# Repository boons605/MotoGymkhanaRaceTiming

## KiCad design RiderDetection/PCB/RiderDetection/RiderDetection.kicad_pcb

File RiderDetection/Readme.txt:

The embedded part of the rider detection was written for the ESP32 platform.
Development hardware used is the ESP32-WROOM-32.
Development environment/framework used is ESP-IDF v4.1-dirty

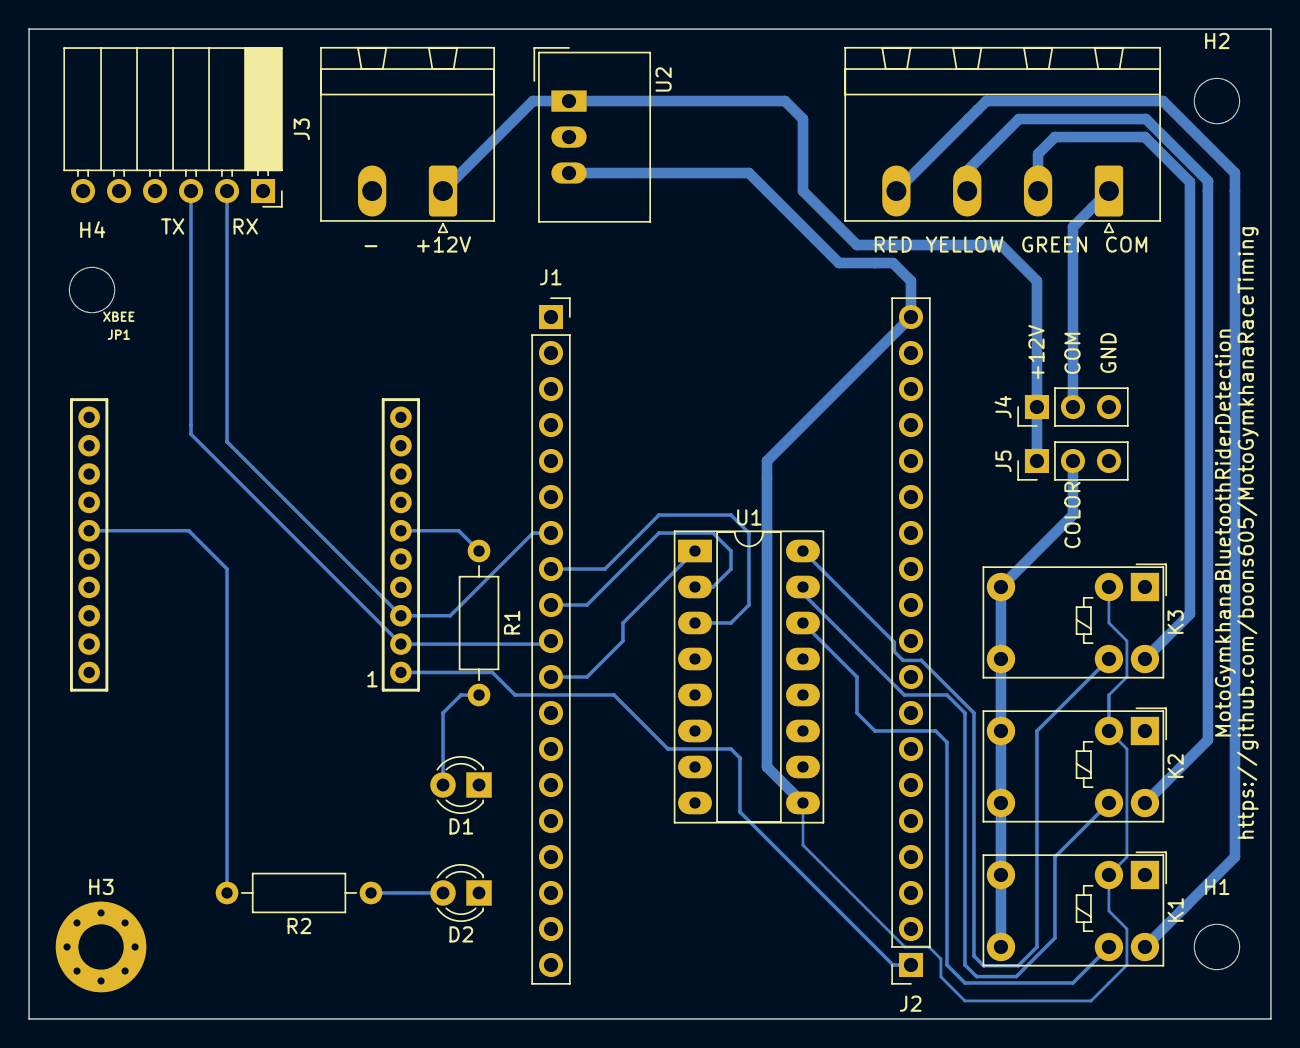
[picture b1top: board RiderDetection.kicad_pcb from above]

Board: 2 copper layers, 87.6 x 69.8 mm, 21 parts (0 on the bottom side), 21 nets.

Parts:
D1, D2: LED; LED_D3.0mm
H1, H2, H4: MountingHole; MountingHole_3.2mm_M3
H3: MountingHole_Pad; MountingHole_3.2mm_M3_Pad_Via
J1, J2: Conn_01x19; PinSocket_1x19_P2.54mm_Vertical
J3: Conn_01x06; PinSocket_1x06_P2.54mm_Horizontal
J4, J5: Conn_01x03_Male; PinHeader_1x03_P2.54mm_Vertical
JP1: XBEE
K1, K2, K3: G5V-1; Relay_SPDT_Omron_G5V-1
PWR0: Screw_Terminal_01x02; PhoenixContact_MSTBA_2,5_2-G_1x02_P5.00mm_Horizontal
R1, R2: 330R; R_Axial_DIN0207_L6.3mm_D2.5mm_P10.16mm_Horizontal
STARTLIGHT0: Screw_Terminal_01x04; PhoenixContact_MSTBA_2,5_4-G_1x04_P5.00mm_Horizontal
U1: ULN2003A; DIP-16_W7.62mm_Socket_LongPads
U2: TSR_1-2450; Converter_DCDC_TRACO_TSR-1_THT

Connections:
+3V3: J2.1, JP1.1
+5V: J2.19, K1.2, K2.2, K3.2, U1.9, U2.3
+12V: J4.1, J5.1, PWR0.1, U2.1
COL_GRN: K3.10, STARTLIGHT0.2
COL_RD: K1.10, STARTLIGHT0.4
COL_YW: K2.10, STARTLIGHT0.3
GND: D1.1, D2.1, H3.1, J1.19, J3.6, J4.3, J5.3, JP1.10, PWR0.2, U1.8, U2.2
unnamed: D1.2, R1.2
unnamed: D2.2, R2.1
unnamed: J1.8, U1.3
unnamed: J1.9, U1.2
unnamed: J1.11, U1.1
unnamed: JP1.6, R1.1
unnamed: JP1.15, R2.2
unnamed: K1.9, U1.14
unnamed: K2.9, U1.15
unnamed: K3.9, U1.16
RXD: J1.7, J3.2, JP1.3
START_COLOR_COM: J5.2, K1.5, K1.6, K2.5, K2.6, K3.5, K3.6
START_COM: J4.2, STARTLIGHT0.1
TXD: J1.10, J3.3, JP1.2

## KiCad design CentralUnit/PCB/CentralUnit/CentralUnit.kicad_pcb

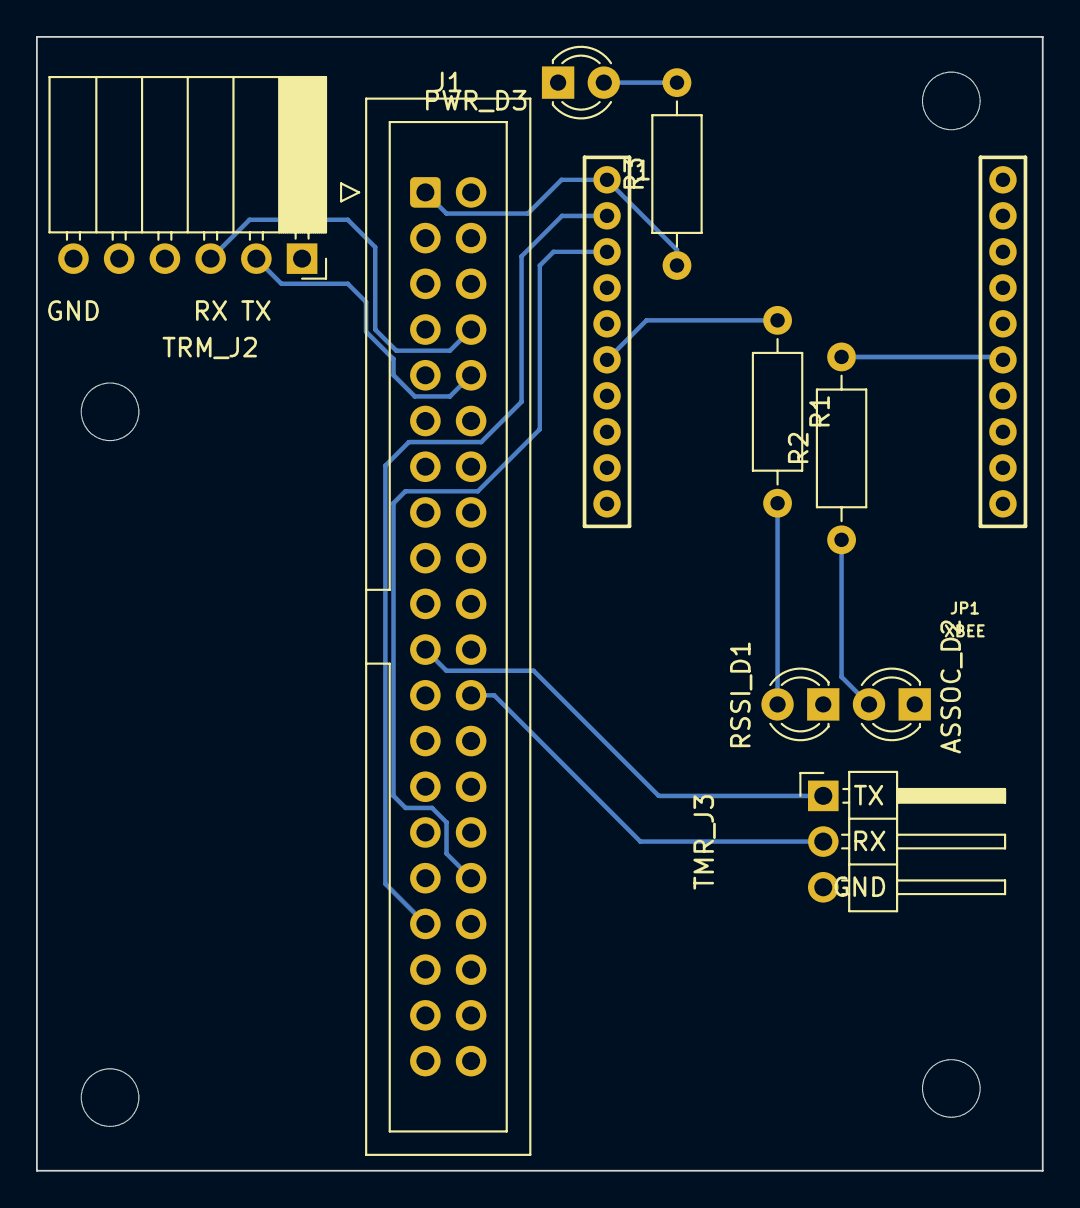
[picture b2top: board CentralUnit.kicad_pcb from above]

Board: 2 copper layers, 55.9 x 63.0 mm, 14 parts (0 on the bottom side), 13 nets.

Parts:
ASSOC_D2: LED; LED_D3.0mm
H1, H2, H3, H4: MountingHole; MountingHole_3.2mm_M3
J1: Conn_02x20_Odd_Even; IDC-Header_2x20_P2.54mm_Vertical
JP1: XBEE
PWR_D3: LED; LED_D3.0mm
R1, R2, R3: 160R; R_Axial_DIN0207_L6.3mm_D2.5mm_P10.16mm_Horizontal
RSSI_D1: LED; LED_D3.0mm
TMR_J3: Conn_01x03_Male; PinHeader_1x03_P2.54mm_Horizontal
TRM_J2: Conn_01x06; PinSocket_1x06_P2.54mm_Horizontal

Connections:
+3V3: J1.1, JP1.1, R3.1
GND: ASSOC_D2.1, J1.39, JP1.10, PWR_D3.1, RSSI_D1.1, TMR_J3.3, TRM_J2.6
unnamed: ASSOC_D2.2, R2.1
unnamed: JP1.6, R1.1
unnamed: JP1.15, R2.2
unnamed: PWR_D3.2, R3.2
unnamed: R1.2, RSSI_D1.2
TMR_RX: J1.24, TMR_J3.2
TMR_TX: J1.21, TMR_J3.1
TRM_RX: J1.8, TRM_J2.3
TRM_TX: J1.10, TRM_J2.2
XBEE_RX: J1.32, JP1.3
XBEE_TX: J1.33, JP1.2

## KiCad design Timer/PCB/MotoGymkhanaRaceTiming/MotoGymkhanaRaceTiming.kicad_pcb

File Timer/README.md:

# MotoGymkhanaRaceTiming

This directory contains files for the STM32 software and the supporting PCB

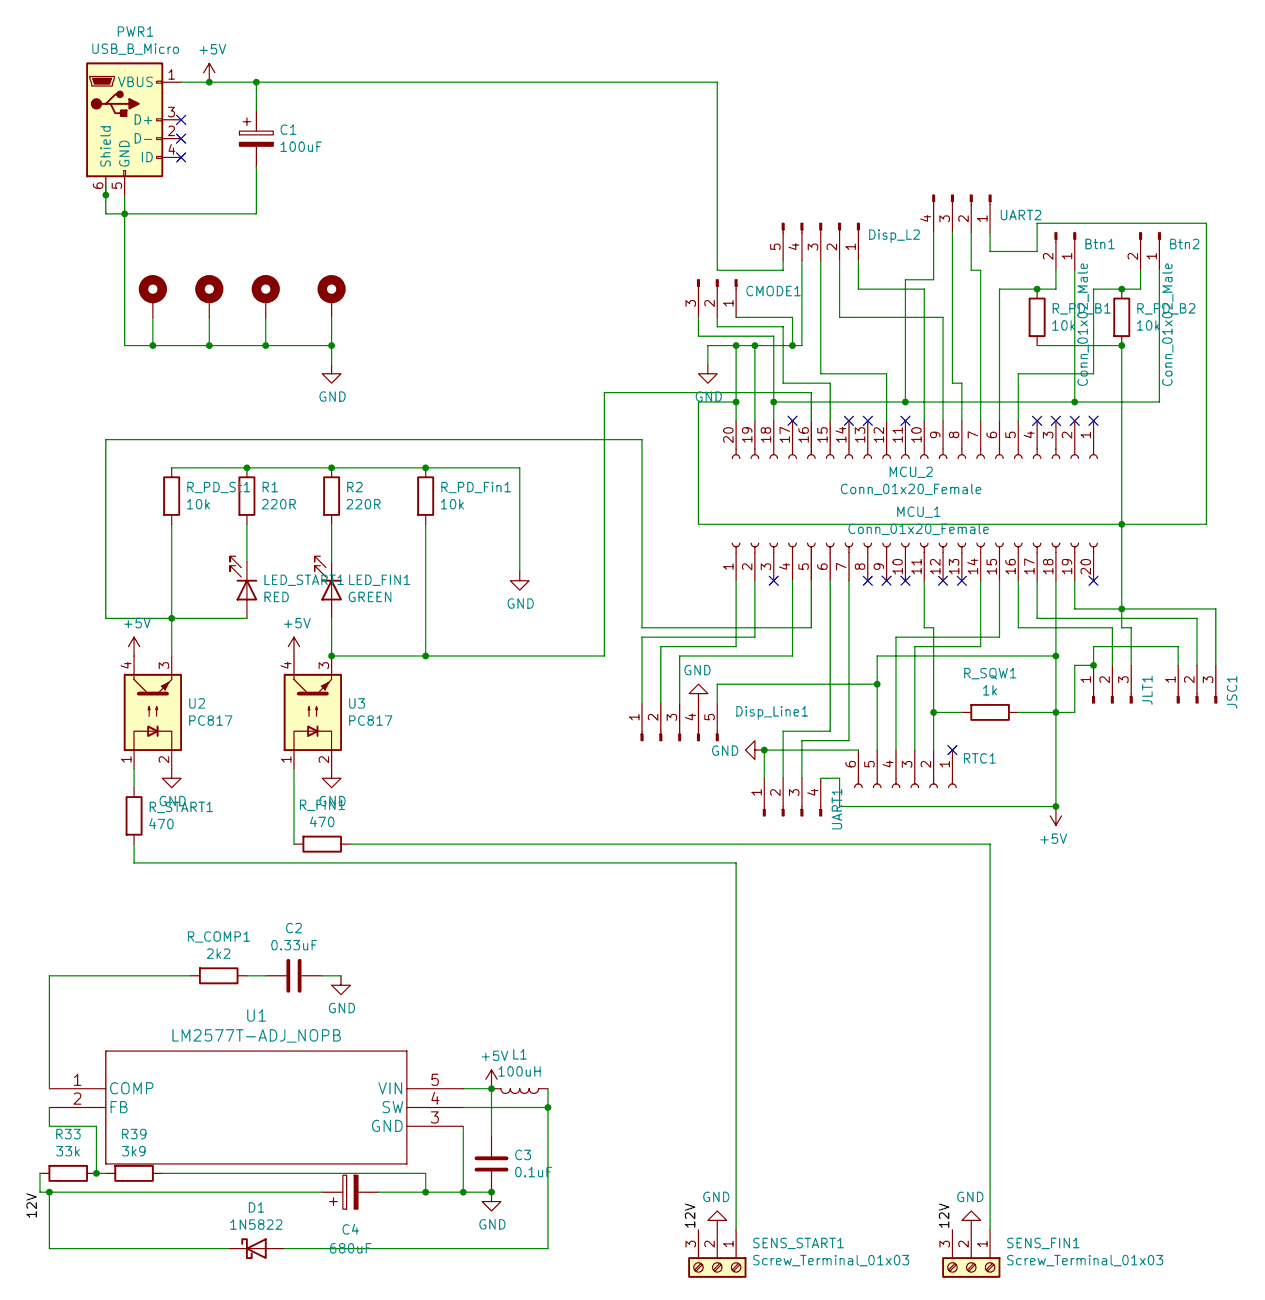
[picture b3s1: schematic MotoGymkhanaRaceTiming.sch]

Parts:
Btn1, Btn2: Conn_01x02_Male; PinHeader_1x02_P2.54mm_Vertical
C1: 100uF; CP_Radial_D8.0mm_P5.00mm
C2: 0.33uF; C_Disc_D4.7mm_W2.5mm_P5.00mm
C3: 0.1uF; C_Disc_D4.7mm_W2.5mm_P5.00mm
C4: 680uF; CP_Radial_D10.0mm_P5.00mm
CMODE1: Conn_01x03_Male; PinHeader_1x03_P2.54mm_Vertical
D1: 1N5822; D_DO-201AD_P15.24mm_Horizontal
Disp_L2: Conn_01x05_Male; DisplayLineConnector
Disp_Line1: Conn_01x05_Male; DisplayLineConnector
H1, H2, H3, H4: MountingHole_Pad; MountingHole_3.2mm_M3_Pad_Via
JLT1: Conn_01x03_Male; PinHeader_1x03_P2.54mm_Vertical
JSC1: Conn_01x03_Male; PinHeader_1x03_P2.54mm_Vertical
L1: 100uH; L_Radial_D7.0mm_P3.00mm
LED_FIN1: GREEN; LED_D5.0mm
LED_START1: RED; LED_D5.0mm
MCU_1, MCU_2: Conn_01x20_Female; PinSocket_1x20_P2.54mm_Vertical
PWR1: USB_B_Micro; USB_Micro-B_Wuerth_614105150721_Vertical_CircularHoles
R1, R2: 220R; R_Axial_DIN0207_L6.3mm_D2.5mm_P10.16mm_Horizontal
R33: 33k; R_Axial_DIN0207_L6.3mm_D2.5mm_P10.16mm_Horizontal
R39: 3k9; R_Axial_DIN0207_L6.3mm_D2.5mm_P10.16mm_Horizontal
RTC1: Conn_01x06_Female; RTC_Socket
R_COMP1: 2k2; R_Axial_DIN0207_L6.3mm_D2.5mm_P10.16mm_Horizontal
R_FIN1: 470; R_Axial_DIN0207_L6.3mm_D2.5mm_P10.16mm_Horizontal
R_PD_B1, R_PD_B2: 10k; R_Axial_DIN0207_L6.3mm_D2.5mm_P10.16mm_Horizontal
R_PD_Fin1: 10k; R_Axial_DIN0207_L6.3mm_D2.5mm_P10.16mm_Horizontal
R_PD_St1: 10k; R_Axial_DIN0207_L6.3mm_D2.5mm_P10.16mm_Horizontal
R_SQW1: 1k; R_Axial_DIN0207_L6.3mm_D2.5mm_P10.16mm_Horizontal
R_START1: 470; R_Axial_DIN0207_L6.3mm_D2.5mm_P10.16mm_Horizontal
SENS_FIN1: Screw_Terminal_01x03; SensorConnector
SENS_START1: Screw_Terminal_01x03; SensorConnector
U1: LM2577T-ADJ_NOPB; LM2577T-ADJ&slash_NOPB
U2, U3: PC817; DIP-4_W7.62mm
UART1, UART2: Conn_01x04_Male; UART

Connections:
+5V: C1.1, C3.1, Disp_L2.5, Disp_Line1.5, JLT1.1, JSC1.1, L1.2, MCU_1.18, PWR1.1 (VBUS), RTC1.5, R_SQW1.1, U1.5 (VIN), U2.4, U3.4, UART1.4; also elsewhere on the board
/12V: C4.1, D1.1 (K), R33.2, SENS_FIN1.3, SENS_START1.3
GND: C1.2, C2.1, C3.2, C4.2, CMODE1.1, Disp_L2.4, Disp_Line1.4, H1.1, H2.1, H3.1, H4.1, JLT1.3, JSC1.3, MCU_1.19, MCU_2.19, MCU_2.20, PWR1.5 (GND), PWR1.6 (Shield), R1.1, R2.1, R39.1, RTC1.6, R_PD_B1.2, R_PD_B2.2, R_PD_Fin1.1, R_PD_St1.1, SENS_FIN1.2, SENS_START1.2, U1.3 (GND), U2.2, U3.2, UART1.1, UART2.1; also elsewhere on the board
unnamed: Btn1.1, Btn2.1, CMODE1.3, MCU_2.18, UART2.4
unnamed: Btn1.2, MCU_2.6, R_PD_B1.1
unnamed: Btn2.2, MCU_2.5, R_PD_B2.1
unnamed: C2.2, R_COMP1.1
unnamed: CMODE1.2, MCU_2.15
unnamed: D1.2 (A), L1.1, U1.4 (SW)
unnamed: Disp_L2.1, MCU_2.10
unnamed: Disp_L2.2, MCU_2.9
unnamed: Disp_L2.3, MCU_2.12
unnamed: Disp_Line1.1, MCU_1.2
unnamed: Disp_Line1.2, MCU_1.1
unnamed: Disp_Line1.3, MCU_1.4
unnamed: JLT1.2, MCU_1.16
unnamed: JSC1.2, MCU_1.17
unnamed: LED_FIN1.1 (K), R2.2
unnamed: LED_FIN1.2 (A), MCU_2.16, R_PD_Fin1.2, U3.3
unnamed: LED_START1.1 (K), R1.2
unnamed: LED_START1.2 (A), MCU_1.5, R_PD_St1.2, U2.3
unnamed: MCU_1.6, UART1.2
unnamed: MCU_1.7, UART1.3
unnamed: MCU_1.11, RTC1.2, R_SQW1.2
unnamed: MCU_1.14, RTC1.3
unnamed: MCU_1.15, RTC1.4
unnamed: MCU_2.7, UART2.2
unnamed: MCU_2.8, UART2.3
unnamed: R33.1, R39.2, U1.2 (FB)
unnamed: R_COMP1.2, U1.1 (COMP)
unnamed: R_FIN1.1, SENS_FIN1.1
unnamed: R_FIN1.2, U3.1
unnamed: R_START1.1, U2.1
unnamed: R_START1.2, SENS_START1.1

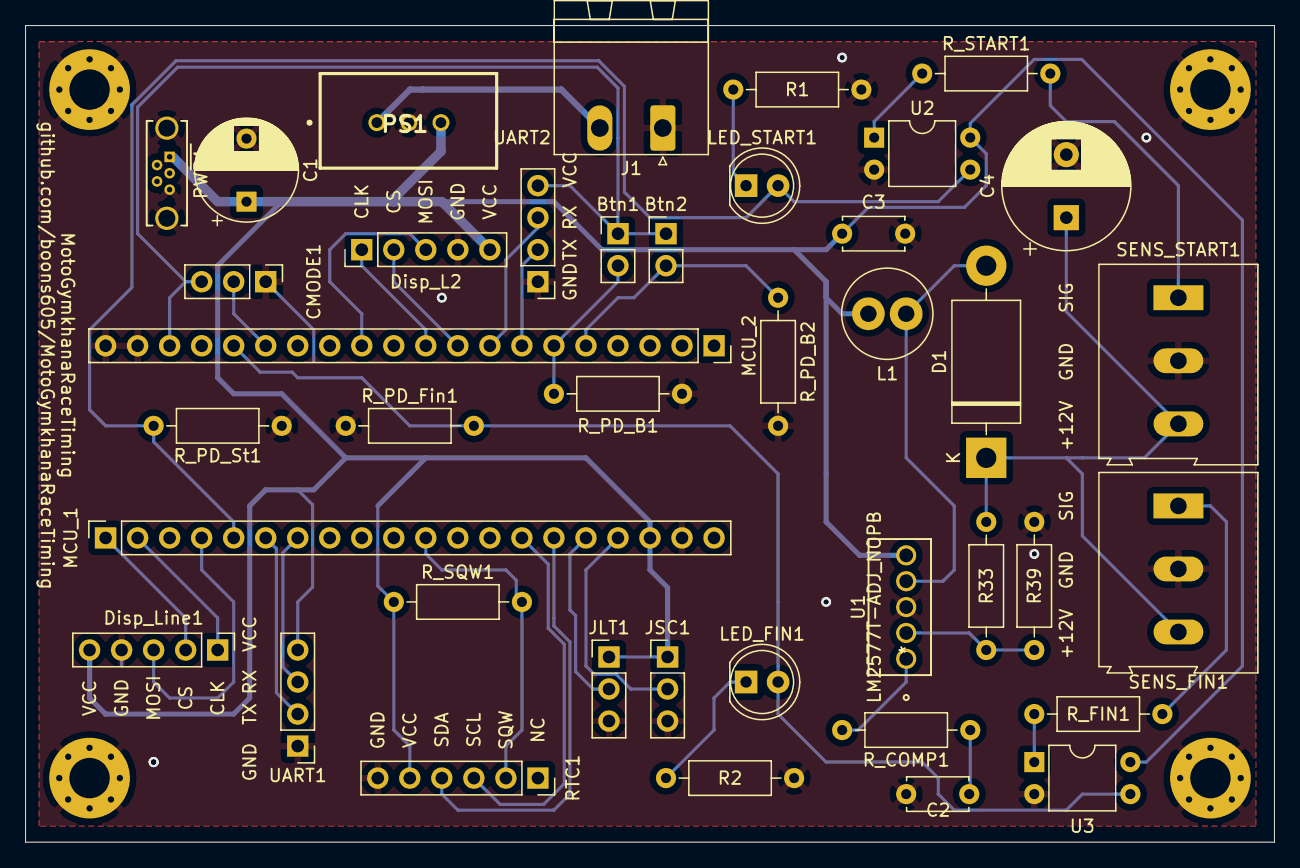
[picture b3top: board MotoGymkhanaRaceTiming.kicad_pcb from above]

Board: 2 copper layers, 99.1 x 64.8 mm, 44 parts (0 on the bottom side), 35 nets.

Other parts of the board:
J1: Screw_Terminal_01x02; PhoenixContact_MSTBA_2,5_2-G_1x02_P5.00mm_Horizontal
PS1: TSR_2-2450; TSR-2

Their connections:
+5V: PS1.3; also elsewhere on the board
GND: J1.1, PS1.2; also elsewhere on the board
unnamed: J1.2, PS1.1

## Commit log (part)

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2020-05-10 Adding files to version control. Resolves #1
2020-05-10 Starting work on implementation of single sensor lap timer logic #2
2020-05-10 Renaming files Updating simulator
2020-05-10 Renaming
2020-05-13 Prescaler booboo
2020-05-15 Display (#4), Laptimer bugs (#3)
2020-05-18 Created diagram to consult users for issue #7
2020-05-18 Display #4
    Energy saving
2020-05-24 Adding PCB files
2020-05-25 Better PCB, now with jumpers (or headers to wire switches to) for configuration
2020-05-26 Implentation of auto configuration for issue #6
    Display optimizations for #4
2020-05-30 Change timer to 100us resolution to achieve millisecond precision in laps #8
2020-06-04 Sensor hardware order list at digikey
2020-06-04 Updating sensor hardware order list
2020-06-12 PCB update
2020-06-13 Update for issue #9
    - Adding text to RTC socket
    - Adding UART2
    - Trace width for 5V net updated
2020-06-13 Preparations for user interface
2020-06-20 User interface:
    - Previous times can now be restored using a button.
2020-11-22 Starting to work on rider detection using BLE iBeacon and ESP32
2020-11-23 Adding PC Test code, nothing implemented yet. Added more communication protocol code, seems we're ready to implement actual functionality now.
2020-11-26 Communication protocol works now, can add device to allowed devices list.
2020-11-27 Distance calculation
2020-12-04 Added functions to list all devices and list allowed devices Packetization untested
2020-12-06 Implemented cleanup of 'old' devices on the embedded device. Made some improvements to the tester.
2020-12-21 Changed environment factor for calculating distance from average RSSI over 4 samples from 2 to 4, to increase accuracy of distance measurement. Still not accurate at short distances, but good enough 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
    Now just sending closest device every 1 second, to ease testing.
    Also fixed bug where a 'cleared' device would start with an average rssi of 0, which would take 4 samples to clear up. This would mess up the distance exponent and therefore mess up the detection of 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
2020-12-21 Updated form layout to make things fit. Changed distance environment factor
2020-12-21 Added correction factor.
    The PC application is getting uglier and uglier.
2020-12-24 Correction factor got lost after a cleanup. Reduced complexity of count functionin manager. All functions now below cyclomatic complexity of 10.
2020-12-25 Adding rider name
2020-12-28 Schematic optimizations
2020-12-28 Creating timer folder
2020-12-28 Adding System Concept drawing
2020-12-28 Issue 10: Added interfaces for edge units and basic commandline
2020-12-29 Issue-10: fixed deprecation warning
2020-12-29 Issue-10: Removed zigbee test code, added communication project
2020-12-29 Issue-10: re-added after ignore
2020-12-30 Issue-10: Added scaffold for race management
2020-12-30 Optimized complexity of RaceTiming, adding some eclipse settings files to ignore list
2020-12-30 Project dependency issue would cause solution not to build
2020-12-30 Adding xbee library
2020-12-30 Issue 14: Starting implementation of communication manager
2020-12-30 Just let me play in there.
2020-12-31 Issue-12: Added some unit tests
2020-12-31 Adding Digi Xbee library instead of ZigBeeNet Adding XbeeNetwork and SerialCommunication implementation classes
2021-01-01 Issue 14: Message transmission over Xbee
2021-01-01 Issue 14: Parsing of incoming data
2021-01-01 Issue 14: Index issue in communication manager, execution order issue in XbeeNetwork, causing double events. Complexity reducation in XbeeNetwork.
2021-01-02 Issue 14: Processing review comments from pull request #16
2021-01-02 Issue-12: Added additional tests for complete lap of events
2021-01-03 Issue-12: Added final tests, fixed issues that came up
2021-01-03 Issue #17: Adding generic Communication Protocol handlers. This protocol is already built into the embedded part of the Rider ID unit. Since for the timer the embedded part of the communication still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
    It seems most of the plumbing for the Rider ID Unit is now in place.
2021-01-09 Issue-12: Added event to signal when a rider is ready to start
2021-01-09 Issue-12: Added finish event
2021-01-09 Issue-12: Various stylecop fixups
2021-01-09 Issue #17, Rider ID Unit implementation
2021-01-11 issue #13 timer communication
2021-01-13 issue #13 timer communication: It's alive!
2021-01-17 Issue-18: Moved RaceSummary and all RaceEvents to Models
2021-01-17 Issue-18: Removed unused test
2021-01-17 issue #13 timer communication: Implementation of thread, introduced more elaborate failure information through event args.
2021-01-23 issue #13 timer communication: Further progress, but it doesn't work exactly as expected yet.
2021-01-24 Issue-18: Fixed race summary serialization
2021-01-28 issue #13 timer communication: Stylecop
2021-01-31 Issue-23: WIP base simulation unit
2021-01-31 issue #13 timer communication: Comments from pull request
2021-01-31 Issue-23: Added cli for starting a simulation. Changed RaceTracker to consume events instead of directly working off handlers
2021-02-07 Issue-23: fixed issue with displaying rider name on DNF in simulation
2021-02-11 Issue 19: Starting schematics for carrier PCB for rider ID
2021-02-13 Issue 19: Schematics for carrier PCB for rider ID
2021-02-22 Issue 19: Carrier PCB for rider ID
2021-03-06 Issue 19: Carrier PCB for rider ID, V2 with corrections
2021-03-07 Issue-15: Added simulation race tracker to startup. Added endpoint fo tracker state
2021-03-07 Issue #27: Start light embedded
2021-03-15 Starting issue #29: Carrier PCB for central unit
2021-03-21 Issue-15: Added wrapping class for handling tracker initialization
2021-03-28 Issue-15: Addded necessary config for reverse proxy
2021-03-28 Issue-15: Added docs and summary file
2021-04-11 Issue #37: Fixing Xbee comms issue
2021-04-11 Issue #37: Fixing Xbee comms issue, resolving comments from pull request #38
2021-04-16 Issue #41: Added unit ID to log statements, added some log statements to track application progress, ensured setting of connected flag on Xbee modules, added statement on initialization of Xbee netwo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
2021-04-18 Issue-32: Added missing calls to add/remove riders. Added additional info to id events
2021-04-18 Issue-15: Added gate options to test unit cli
2021-04-22 Issue-32: Added appropriate handlers for id unit exit events
2021-04-24 Issue-32: Added more tests
2021-04-25 Issue-34: Added display unit calls and display clear
2021-04-25 Issue-34: Remove display clear time, unit already does it
2021-04-27 Making detection range configurable
2021-04-30 Delayed startup of display drivers
2021-05-01 Issue-45: Added error handling to State endpoint
2021-05-01 Issue #49: Made all fields in the Config request required
2021-05-01 Issue #49: Fixed typo
2021-05-01 Issue #45: Added HasState bool to RaceManager. Fixed end id match time to 10 secs for unit tests
2021-05-01 Issue #46 could also be fixed in software apparently. Software now supports both startup delay and it clears all registers in the display device before initializing.
2021-05-01 Fixed issue where riders were added to stop id unit too soon
2021-05-02 Issue #54: Clear riders on service startup
2021-05-13 Issue-33: Added handlers for manual penalty, dsq and dnf events. Added tests for manual dnf
2021-05-15 Issue-33: Added tests for DSQ events
2021-05-15 Issue-33: Added endpoints for dnf, dsq and penalty
2021-05-22 Issue-33: Added dsq to lap ordering
2021-05-23 Issue-58: stub implementation of web api polling
2021-05-23 Issue-58: implemented some of the web interface methods
2021-05-29 Issue-58: Added run command
2021-05-29 Issue-58: Added some logging to the polling loop
2021-05-29 Issue-58: Added http error handling to polling loop
2021-05-29 Issue-58: Fixed some id issues and post laptime in millis instead of micros
2021-05-30 Adding logging
2021-05-31 Adding log statements
2021-06-19 Issue-56: Test Aanpassing
    Dit is een test aanpassing om te kijken hoe ik iets aanpas.
2021-06-19 Issue-56: Fixed issue wher lap endpoints throw exception if there is no race running
2021-06-27 Issue-56: Added test js file
2021-06-27 Issue-56-web-interface
    Tussentijdse progressie. Eerste opzet interface. Work in progress.
2021-07-10 Fixes #62: Can now control the new display
2022-03-19 Issue-56: Added more data to interface
2022-03-27 Issue-56: Cleared up rider names in some log messages
2022-03-27 Issue-56: Added logs page
2022-03-27 Improving log output
2022-03-27 Issue-56: Changed Beacons list from id unit to single closest beacon
2022-03-27 Adding rider name to closest beacon display
2022-06-23 Bump Newtonsoft.Json from 12.0.3 to 13.0.1 in /CentralUnit/Models
    Bumps [Newtonsoft.Json](https://github.com/JamesNK/Newtonsoft.Json) from 12.0.3 to 13.0.1.
    - [Release notes](https://github.com/JamesNK/Newtonsoft.Json/releases)
    - [Commits](https://github.com/JamesNK/Newtonsoft.Json/compare/12.0.3...13.0.1)
    ---
    updated-dependencies:
    - dependency-name: Newtonsoft.Json
2022-12-08 Bump Newtonsoft.Json from 12.0.3 to 13.0.2 in /CentralUnit/Models
    Bumps [Newtonsoft.Json](https://github.com/JamesNK/Newtonsoft.Json) from 12.0.3 to 13.0.2.
    - [Release notes](https://github.com/JamesNK/Newtonsoft.Json/releases)
    - [Commits](https://github.com/JamesNK/Newtonsoft.Json/compare/12.0.3...13.0.2)
    ---
    updated-dependencies:
    - dependency-name: Newtonsoft.Json
2022-12-11 Issue-56: We decided to take the system in a different direction. The web interface in this solution will only provide api endpoints, no ui
2022-12-17 Eerste opzet geupload
2022-12-25 Starting work on embedded timer that supports multiple riders
2022-12-26 Issue-68: Removed files for web page. Removed Beacons endpoint
2022-12-26 Issue-68: wip retooling race tracker for manual time matching
2022-12-29 Issue-68: wip fixing unit tests
2022-12-29 Bugfixes while testing
2023-01-07 Issue-68: tests compile again
2023-01-08 Issue-68: fixed tests
2023-02-04 New Functions added
    The UI is now close to how the final version will be. Added some simulation so it can be demonstrated and tested without API.
2023-02-11 Issue-68: Implemented some endpoints
2023-02-18 Issue-68: fixed some serialization units
2023-02-18 Issue-68: added debug endpoint to trigger timing unit
2023-03-12 Issue-68: added cors to web api, added sample ajax request to main js script
2023-06-07 Adding HTML/CSS/JS files to Visual Studio project, enabled static files to be served by integrated web server
2023-06-07 Attempt to restore netbeans project
2023-10-25 Issue-68: fixed mock racte tracker
2023-10-27 Added API functionality
    not finished
2023-10-28 Issue-68: GetRiders endpoint now respects insert order
2023-10-29 Issue-68: added new andpoint for changing rider start position
2023-11-02 Stable version of UI
    Only DSQ does not work.
    Given penalties cannot be displayed.
2023-11-02 display result
    After a rider is confirmed to stop by user, the result time in ms (obtained from server) is now displayed.
2023-11-06 Facilitating easy testing by not having to load the simulation through an endpoint every time.
2023-11-06 Adding hardware config for easy startup
2023-11-17 Ignore files
2023-11-19 UI responds to Race Manager not running or reachable
2023-11-19 Added Trigger Buttons
    In the GUI, you can now manually trigger a gate event with the keyboard keys "a" and "o".
    A = start event
    O = stop event
    Fixed the us/ms problem on UI side (factor 1000)
2023-11-20 Added a results overview
2023-11-20 Some changes in display
2023-11-26 Issue-84: ignore end timer events when no riders are on track
2023-11-30 DSQ status is now visible in UI
2023-12-09 Issue-84: finished off tests
2023-12-18 fixed a bug
2024-02-17 Correcting gate IDs
2024-02-18 Issue 89: Sending display data would trigger sending latest timestamp because flag was set high
2024-02-18 Fix clearing display

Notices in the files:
parts and their libraries:
Copyright 2016 Accelerated Designs. All rights reserved.
